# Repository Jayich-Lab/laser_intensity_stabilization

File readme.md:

# Laser Intensity Stabilization
<div align="center">

</div>

[Development Notebook](https://docs.google.com/document/d/1RtXi4E6TiI_Ld4MZSRgFrHrQVlKGbRzDl3qZmrDYwTk/edit#)

We are aiming to stabilize intensity of laser to a fluctuation range of plus-minus 1% using Acousto-Optic Modulator (AOM) for a long timescale (in the order of days). This stabilization will improve the precision of experiments that use laser beams.

## Table of Contents
- [Motivation](#Motivation)
  - [P 3/2 Life Measurement](#P-32-Life-Measurement)
  - [Problems](#Problems)
  - [Goal](#Goal)
- [List of Components](#List-of-Components)
- [Schematics](#Schematics)
  - [Experiment Setup Schematics](#Experiment-Setup-Schematics)
  - [Acousto-Optics Modulator (AOM)](#Acousto-Optics-Modulator-AOM)
  - [Red Pitaya](#Red-Pitaya)
  - [Voltage Variable Attenuator (VVA)](#Voltag-Variable-Attenuator-VVA)
- [Feedback Loop](#Feedback-Loop)
  - [PID Controller](#PID-Controller)
  - [Code](#Code)
  - [Continuous (CW) Feedback](#Continuous-CW-Feedback)
  - [Pulsed Feedback](#Pulsed-Feedback)
- [Iterations](#Iterations)
  - [PI Stabilization](#PI-Stabilization)
  - [I Stabilization](#I-Stabilization)
- [Future Plans](#Future-Plans)
- [Contributors](#Contributors)

# Motivation
## P 3/2 Life Measurement
<div align="center">

</div>
We want to measure the lifetime of the P 3/2 lifetime of the radium-226 ion. For this measurement, we need to stabilize a detuned 802 nm laser which will be used for probing the  D 5/2 to P 3/2 transitions. The need for laser intensity stabilization comes from the concept of Rabi flopping. When we raise an ion from its ground state to an excited state, it doesn’t simply remain excited; rather, it oscillates back and forth from the ground state to the excited state at a frequency known as the Rabi frequency. The Rabi frequency is directly proportional to the laser intensity. If the laser intensity is not stable, then the excitation oscillation will shift. We will end up with ions between the excited and ground state, which will increase the systematic errors in our measurements. 

## Problems
Laser intensity drifts with time, and the amplitude drift could result in un-precise energy level transition, which affects energy shift induced by ac-stark shift of detuned laser. This unstable laser intensity affects the precision of Ra-226 excitation.

## Goal
Our goal for this research is to find a laser stabilization method that works for any lasers with any desired intensity. Users are able to manually set the desired intensity. The proportional and integral constants in the PID controller will be able to change on its own corresponding to the input signals.

# List of Components

- Photo Diode: [PDA10A2](https://www.thorlabs.com/thorproduct.cfm?partnumber=PDA10A2)
- Acousto Optic Modulator: [ATM-802DA1](https://intraaction.com/wp-content/themes/Divi/pdf/ATMModSeries08991.pdf)
- Laser: [SYNCROLASE-100](https://en.yuyiparts.com/aerotech-syncrolase-100-helium-neon-laser.html)
- Voltage Controlled Oscillator: [ZX95-100-S+](https://www.minicircuits.com/WebStore/dashboard.html?model=ZX95-100-S%2B)
- Voltage Variable Attenuator: [ZX73-2500-S+](https://www.minicircuits.com/WebStore/dashboard.html?model=ZX73-2500-S%2B)
- RF Amplifier: [ZHL-1-2W+](https://www.minicircuits.com/WebStore/dashboard.html?model=ZHL-1-2W%2B)

# Schematics
## Experiment Setup Schematics
<div align="center">

</div>

First, the laser beam [1] is transmitted by the fiber and goes through the two fiber ports [2]. It then is received by the [Acousto-Optic Modulator (AOM)](#Acousto-Optics-Modulator-AOM) [3], which diffracts the light to different intensity. We use the first order beam in our project. Next, the beam coming out from the AOM goes through the PBS (Polarizing Beam Splitter) [4] and the NPBS (Non-Polarizing Beam Splitter) [5]. These two beam splitters split the light and control the amount of light that goes into the ion trap [6] and the photodiode [7]. We choose an NPBS that splits 90 percent of the light and lets 10 percent of the power go into the photodiode. The photodiode is the detector of laser intensity in our project. It converts the light signal into voltage, which can then be received and analyzed by the PID program in Red Pitaya. The photodiode generates a voltage signal in the range of ± 4 volts and outputs it to the Red Pitaya. A ¼ divider [8] is put between the photodiode and the Red Pitaya to compensate the limitation that Red Pitaya can only take a voltage from -1 to 1 volt. A PID program is built in [Red Pitaya](#Red-Pitaya) [9]. It collects signals from the photodiode and compares it to a setpoint voltage to create an error signal. The Red Pitaya will then return this DC gain error signal and send it to a [voltage variable attenuator (VVA)](#Voltage-Variable-Attenuator-VVA) [10]. VVA receives this DC gain signal as well as an RF reference signal sent from the VCO (voltage control oscillator) [11], and it will output an attenuated RF gain with attenuation determined by the input control voltage (see the attenuation graph in the VVA section). The RF gain is then amplified by an RF amplifier [12] and sent back into the AOM to alter the intensity that goes through it.

## Acousto-Optics Modulator (AOM)
<div align="center">

</div>

An AOM uses the acousto-optic effect, which is similar to the Bragg diffraction, to diffract and shift the frequency of the incident light. The acousto-optic effect describes the diffraction of light by acoustic waves. The basis of this effect is a general effect of photoelasticity consisting in the change of the medium permittivity under the action of a mechanical strain. With the acousto-optic effect, the amount of light diffracted by the sound wave depends on the intensity of the sound. Thus, we use the intensity of the sound to modulate the intensity of the light.

For our project, we choose the first order beam from the AOM. The difference between each order beam is that they have different dynamic ranges. The dynamic range is the ratio between the largest and smallest values of the intensity that can be outputted by the AOM. For the zeroth order beam, the intensity can be attenuated from 100 percent to 20 percent, which provides a dynamic range from 100 to 300; while for the first order beam, the intensity can be attenuated from 85 percent to 0 percent, which provides a dynamic range from 100 all the way to infinity. Thus, we choose the first order beam for our project to have a larger dynamic range.

The intensity of the first order beam is controlled by the control signal that goes into the AOM. When the control signal increases, the intensity increases correspondingly. We adjust the intensity of the laser using this property of the AOM.

## Red Pitaya
<div align="center">

</div>

Red Pitaya is an affordable, PC based, multi instrument. It acts as the brain of our project, which takes up the role of PID controller for the feedback loop (Discussed in Feedback Loop Section). Signal coming from the photodiode is received by the DAC portal of the Red Pitaya, and after the PID program an output signal will be sent out from the ADC portal to the voltage variable attenuator (VVA).

## Voltage Variable Attenuator (VVA)
<div align="center">

</div>

Attenuators are transmission line components used to reduce the input power in a system by a predetermined amount. It is operated throughout its entire dynamic range. Different from fixed attenuators, variable attenuators can be controlled to vary the attenuation level of the device with a number of different methods. A voltage variable attenuator, the VVA, has its attenuation controlled by the voltage. The typical attenuation of the VVA we use, ZX73-2500+ attenuator, is shown in the figure below.
<br>
<div align="center">

</div>

From the figure above, we can see that the attenuation of our ZX73-2500+ attenuator is non-linear, with the curve relatively linear and flat at control voltage range 0 to 0.5 volts and at high voltage. These linear regions imply that at these two control voltage ranges, the attenuation of the VVA does not change dramatically under large control voltage change. This property of the VVA helps to diminish the overcompensation of the PID program and prevent it from destroying the whole feedback loop. An overcompensation of the PID program means that the PID overcompensates for every positive error and creates an even larger error in the negative direction (and vice-versa). With a VVA in the circuit, the overcompensation from the PID feedback can be diminished and it will not cause serious failure in the stabilization. To achieve high precision, we require the input control signal at higher voltage. We choose 4-12 volts as our range of control voltage in our project.

# Feedback Loop
## PID Controller
<div align="center">

</div>

Red Pitaya is remotely controlled using a client on a computer via an internal network. After receiving the signal, the pitaya runs a python script (discussed in [Code](#Code)) section, compares the input voltage to the setpoint voltage, and applies a control signal, C, which depends on the proportional, integral and differential terms of the error signal. The relationship can be seen in the equation above. We neglected the differential term for our setup as we weren’t concerned with stabilizing at high frequency (laser fluctuations tended to be low frequency). The control signal from the pitaya goes through an operational amplifier which increases the control range from ± 1 volt to 4 and 12 volts. The [Voltage Variable Attenuator (VVA)](#Voltage-Variable-Attenuator-VVA) section explains why we want to be in the 4 -12 voltage range. The control signal was also sent to an oscilloscope at the same time. The majority of the data was taken on an oscilloscope. The data from the oscilloscope was read by a server on the computer and sent to the red pitaya. The computer (server and client) are constantly communicating with the red pitaya during  the feedback loop. 

## Code
The programming was mainly done on the red pitaya using python and the PyRPL module, which has python defined classes for controlling the pitaya outputs and inputs. The PyRPL code was written onto a server, and a client was then made using that server. 
There was also a simpler script made for an independent laser intensity stabilization setup using an Arduino due. The code is above under “PI_Stabilization.ino”. The Arduino presents versatility as it uses C++, a widely accessible programming language. On the other hand, the red pitaya can either be programmed using the limited PYRPL module or the native language of the pitaya, Verilog, which is less accessible. 
Either the Arduino or the pitaya is sufficient for stabilization. Still, when it comes to pulsed feedback (discussed shortly), the Arduino is a better choice as C++ is easier to work with than Verilog. 

## Continuous (CW) Feedback
<div align="center">

</div>

We need to identify a clear distinction between continuous and pulsed feedback. In this experiment, we are applying continuous waveform (CW) feedback. We are continuously reading data and stabilizing it over time. The picture above illustrates a summary of our CW feedback in a rectangle on the right. Generally, in ion trap experiments, laser beams are sent to the ion trap in pulse sequences (on the order of microseconds). We can create a stabilized pulsing laser by placing a second AOM after the laser is stabilized. The second AOM will receive a signal that turns it “on” or “off,” This way, we have a pseudo pulsed feedback setup. 

## Pulsed Feedback
<div align="center">

</div>
We created pseudo pulsed feedback, but what does pulsed feedback look like? Unlike CW feedback, in pulsed feedback, we only take data on short intervals (µs). The above graph models a pulse sequence where the laser is on for µs and off for ms. During the period the laser is on, a microcontroller collects data and generates an error signal E1. When the laser is off, the microcontroller outputs a constant dc offset. After the laser is turned on again, a fixed dc voltage (red line) is outputted based on the error signal E1. This process continues for all pulses.
<br>
*Note only CW feedback was used in this project 

# Iterations
## PI Stabilization
<div align="center">

</div>
<br>

Laser intensity was stabilized to ± 0.2%, which surpasses our goal of ± 1%. The blue plot is the signal received by the photodiode, the orange curve is the control signal output by the red pitaya, and the green line is the stabilized signal.  We took the data in 8 hours and found no drifts in the stabilization, which indicates that our setup is robust since it maintains the same intensity while environmental parameters such as temperature change. Using only the P and I terms, we were able to minimize the initial noise by a factor of 200. 
<br><br>

<div align="center">

</div>
<br>

Looking more closely at the stabilized signal, we can see no long-term drift; the signal only oscillates at high frequency. This high-frequency noise can be accounted for by the internal noise of the photodiode. The ± 0.2% fluctuation in our data was partly correlated to the photodiode uncertainty; the rest of the noise comes from the control signal output by the pitaya. The above data set was preliminary data and demonstrated the sufficiency of our stabilization for the P 3/2 life measurement. 

## I Stabilization
<div align="center">

</div>

Using 802 nm laser light (20% intensity fluctuation without stablilization), we stablilized the laser to average within ± 0.1% of our setpoint intensity. Extreme peaks during stablization still stayed within ± 0.3% of setpoint.  Long term drift of intensity from 802 nm is no longer a problem with this intensity stabilizer. The graph above was taken  on the laser that was used for the P 3/2 life time measurement. 

Observations:
1. It was found that **omitting** the proportional term for PID control was more stable than including proportional control.
2. The lower the control voltage (shown in the bottom graph as it slopes downward), the less stablity we get due to the VVA response curve at different voltages.

# Future Plans
<div align="center">

</div>
<br>

There are some issues with our current pseudo pulsed feedback setup. 1) We can’t stabilize the laser intensity right before the beam reaches the ion trap; it has to go through different optics before reaching the trap, which means it will incur some extra noise that we can’t currently stabilize. 2) The second AOM (the one receiving pulsed signal) changes how fast it can turn on and off based on the environmental temperature. 3) Our current setup, as you can see from the picture above, uses too many separate power supplies, which makes it difficult to set up and apply to any measurement. 
Potential solution: utilize an [Arduino DUE](https://store.arduino.cc/usa/due) to make independent pulsed feedback. This would eliminate the second AOM and allow us to stabilize the laser light right before it reaches the ion trap.We would also be able to make an integrated power supply, making our stabilization more compact and robust. 

# Contributors
This project is made for CS 15C class by Chaoshen Zhang, Sam Gebretsadkan, Vivian Liao and Rei Landsberger.

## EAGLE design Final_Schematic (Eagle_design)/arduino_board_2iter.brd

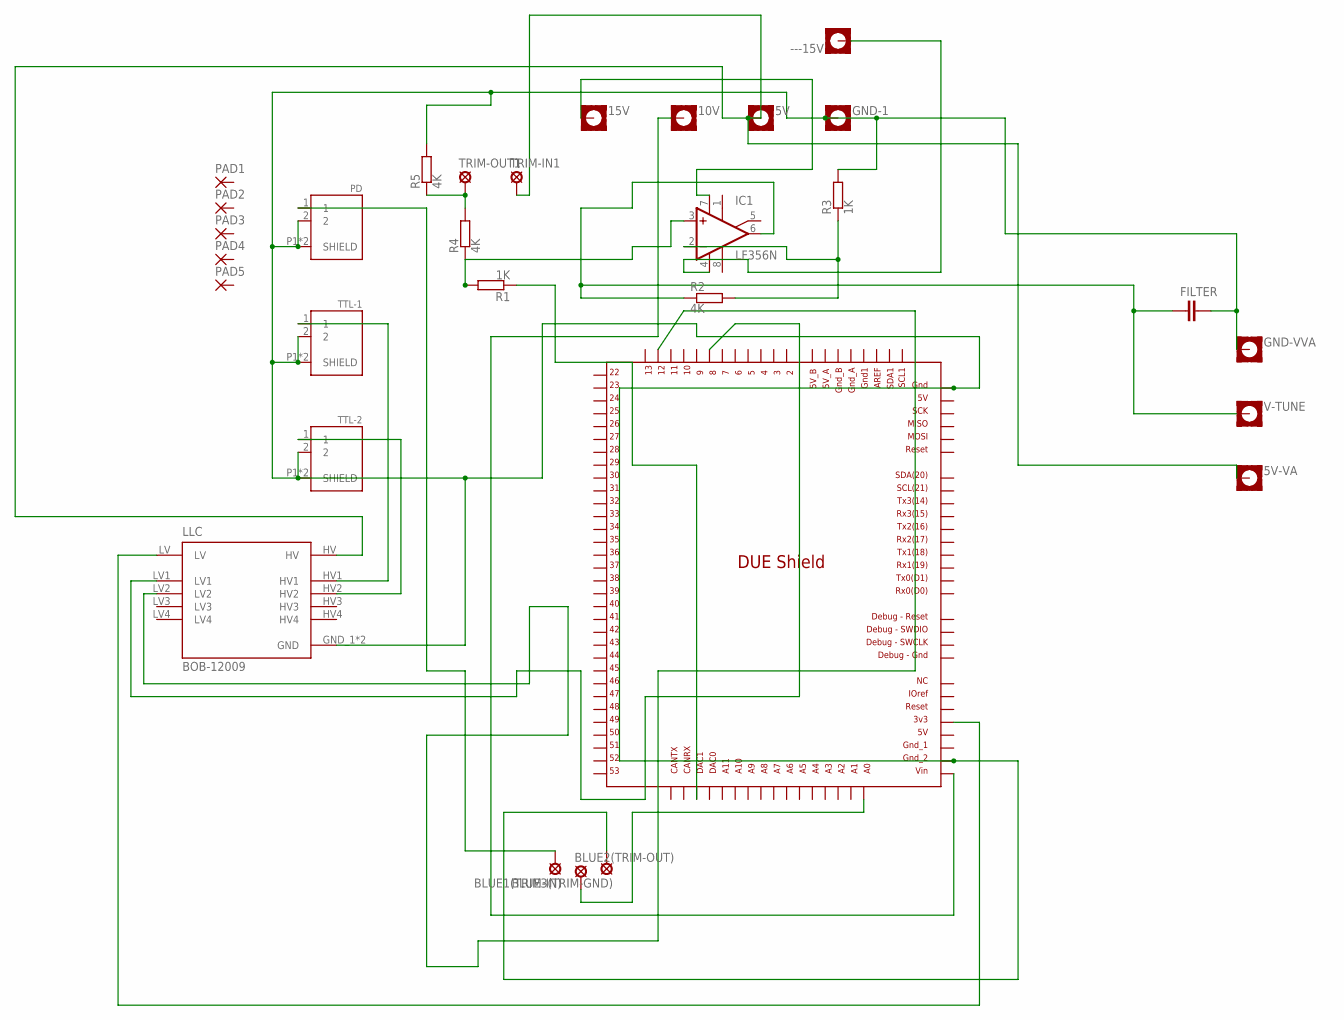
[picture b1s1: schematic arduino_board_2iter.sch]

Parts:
5V, 5V-VA, 10V, 15V: MOUNT-PAD-SQUARE2.8; 2,8-PAD-SQUARE
---15V: MOUNT-PAD-SQUARE2.8; 2,8-PAD-SQUARE
BLUE1(TRIM-IN), BLUE2(TRIM-OUT), BLUE3(TRIM-GND): LSP10
FILTER: C-EUC1812K; C1812K
GND-1: MOUNT-PAD-SQUARE2.8; 2,8-PAD-SQUARE
GND-VVA: MOUNT-PAD-SQUARE2.8; 2,8-PAD-SQUARE
IC1: LF356N; DIL08
LLC: BOB-12009; CONV_BOB-12009
PAD1, PAD2, PAD3, PAD4, PAD5: 1,6/0,9
PD: 1-1337543-0; CONN_1-1337543-0
R1, R3: 1K; SMS-0
R2, R4, R5: 4K; SMS-0
TRIM-IN1: LSP10
TRIM-OUT1: LSP10
TTL-1, TTL-2: 1-1337543-0; CONN_1-1337543-0
U$1: DUE(NORMAL)
V-TUNE: MOUNT-PAD-SQUARE2.8; 2,8-PAD-SQUARE

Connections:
GND: BLUE3(TRIM-GND).MP, FILTER.2, GND-1.B2,8, GND-VVA.B2,8, LLC.GND_1 (GND), LLC.GND_2 (GND), PD.2, PD.P1 (SHIELD), PD.P2 (SHIELD), R3.1, R5.1, TTL-1.2, TTL-1.P1 (SHIELD), TTL-1.P2 (SHIELD), TTL-2.2, TTL-2.P1 (SHIELD), TTL-2.P2 (SHIELD), U$1.5V_ICSP, U$1.GND_2
unnamed: IC1.3 (+IN), R1.1, R4.2
unnamed: FILTER.1, IC1.6 (OUT), R2.2, V-TUNE.B2,8
unnamed: IC1.2 (-IN), R2.1, R3.2
unnamed: 10V.B2,8, U$1.VIN
unnamed: R1.2, U$1.DAC1
unnamed: 15V.B2,8, IC1.7 (V+)
unnamed: LLC.LV, U$1.3V3
unnamed: LLC.HV1, TTL-1.1
unnamed: LLC.HV2, TTL-2.1
unnamed: BLUE1(TRIM-IN).MP, PD.1
unnamed: 5V.B2,8, 5V-VA.B2,8, LLC.HV, TRIM-IN1.MP
unnamed: LLC.LV2, U$1.12
unnamed: BLUE2(TRIM-OUT).MP, U$1.A0
unnamed: R4.1, R5.2, TRIM-OUT1.MP
unnamed: ---15V.B2,8, IC1.4 (V-)
unnamed: LLC.LV1, U$1.8

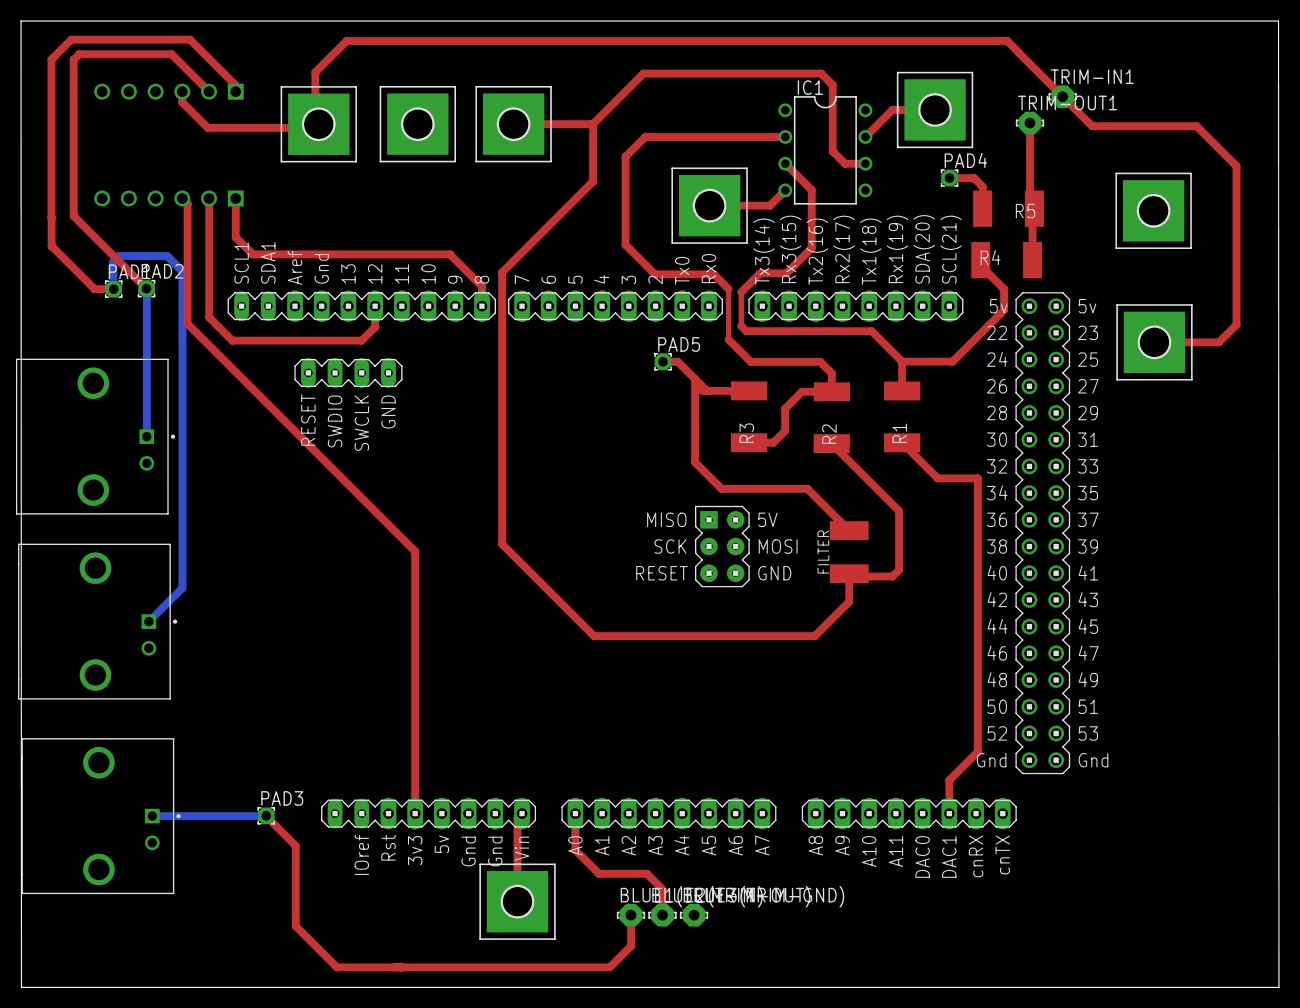
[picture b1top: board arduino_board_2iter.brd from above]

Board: 2 copper layers, 119.6 x 91.9 mm, 30 parts (1 on the bottom side), 17 nets.

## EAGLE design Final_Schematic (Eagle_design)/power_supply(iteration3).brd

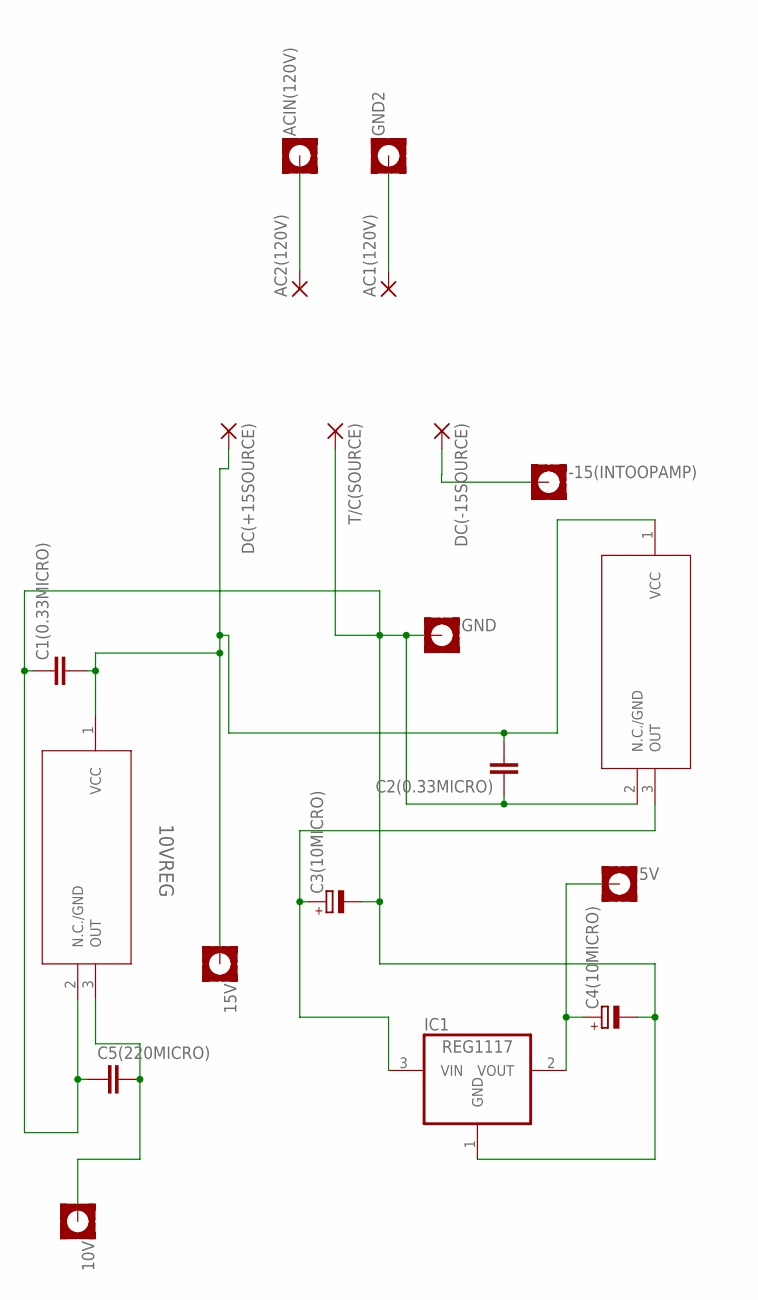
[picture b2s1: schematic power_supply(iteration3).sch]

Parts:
5V, 10V, 15V: MOUNT-PAD-SQUARE2.8; 2,8-PAD-SQUARE
10VREG, 10VREG1: BAJ0BC0T; TO220FP-3_ROM
-15(INTOOPAMP): MOUNT-PAD-SQUARE2.8; 2,8-PAD-SQUARE
AC1(120V), AC2(120V): 3,81/1,4
ACIN(120V): MOUNT-PAD-SQUARE2.8; 2,8-PAD-SQUARE
C1(0.33MICRO), C2(0.33MICRO): C-EU025-025X050; C025-025X050
C3(10MICRO), C4(10MICRO): CPOL-EUE2.5-6; E2,5-6
C5(220MICRO): C-EUC1812K; C1812K
DC(+15SOURCE): 3,81/1,4
DC(-15SOURCE): 3,81/1,4
GND, GND2: MOUNT-PAD-SQUARE2.8; 2,8-PAD-SQUARE
IC1: REG1117; SOT223_HEATSINK
T/C(SOURCE): 3,81/1,4

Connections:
unnamed: 10VREG.1 (VCC), 10VREG1.1 (VCC), 15V.B2,8, C1(0.33MICRO).2, C2(0.33MICRO).2, DC(+15SOURCE).1
unnamed: 10V.B2,8, 10VREG.3 (OUT), C5(220MICRO).2
unnamed: AC2(120V).1, ACIN(120V).B2,8
unnamed: 10VREG1.3 (OUT), C3(10MICRO).+, IC1.3 (VIN)
unnamed: AC1(120V).1, GND2.B2,8
unnamed: -15(INTOOPAMP).B2,8, DC(-15SOURCE).1
unnamed: 10VREG.2 (N.C./GND), 10VREG1.2 (N.C./GND), C1(0.33MICRO).1, C2(0.33MICRO).1, C3(10MICRO).-, C4(10MICRO).-, C5(220MICRO).1, GND.B2,8, IC1.1 (GND), T/C(SOURCE).1
unnamed: 5V.B2,8, C4(10MICRO).+, IC1.2 (VOUT)

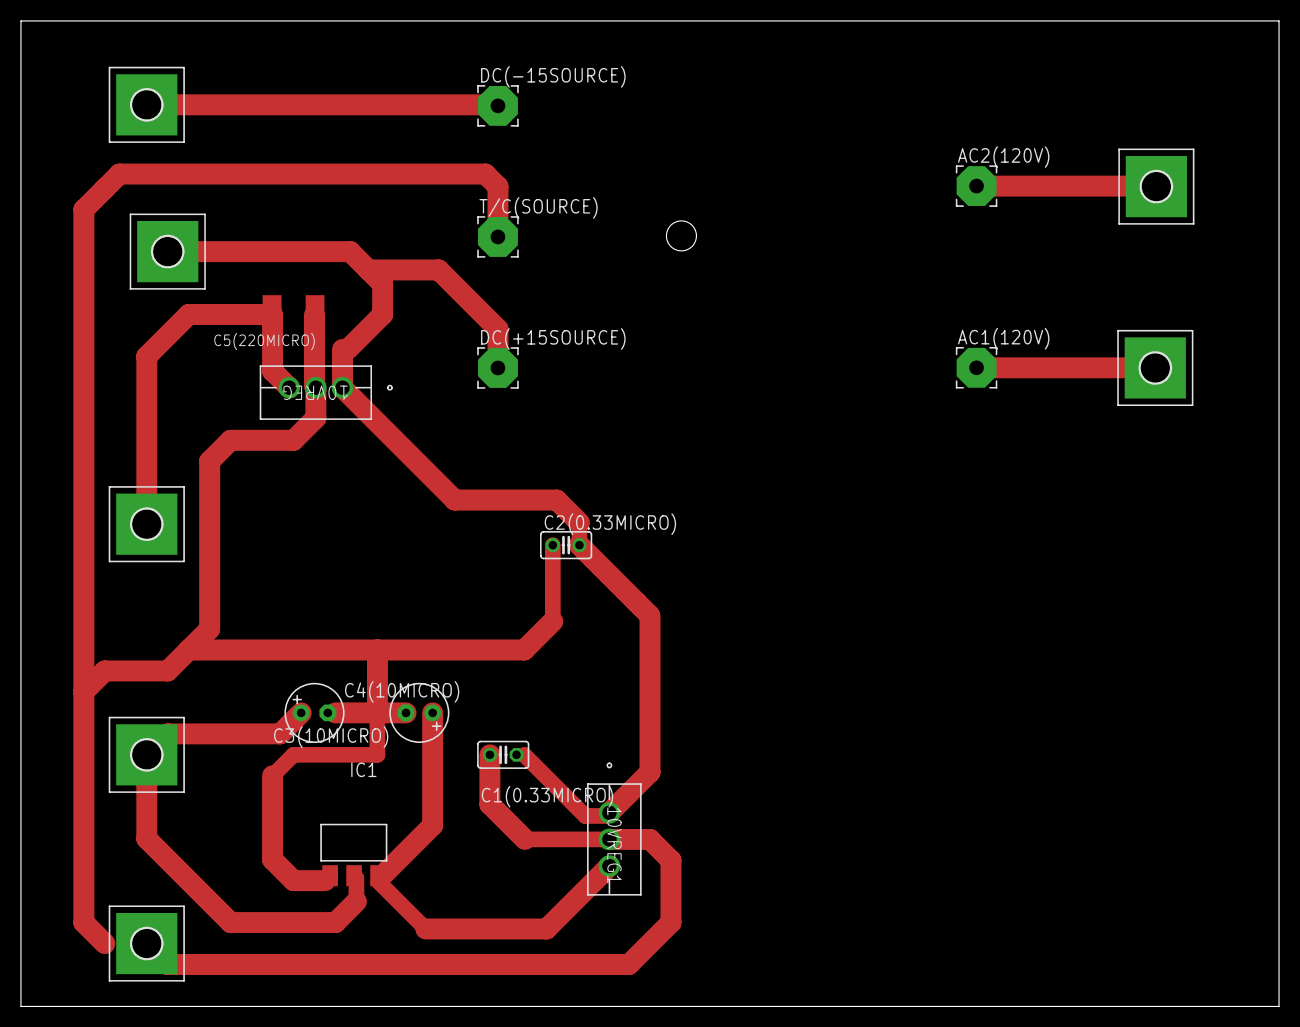
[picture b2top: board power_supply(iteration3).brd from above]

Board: 2 copper layers, 120.0 x 94.0 mm, 20 parts (0 on the bottom side), 8 nets.

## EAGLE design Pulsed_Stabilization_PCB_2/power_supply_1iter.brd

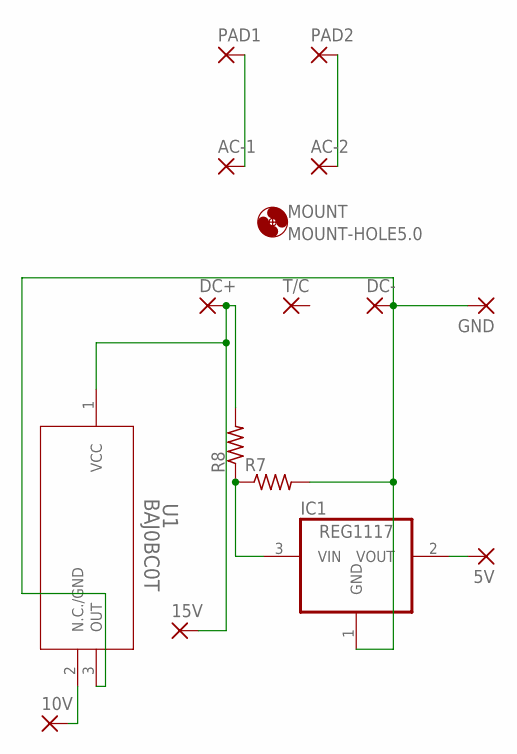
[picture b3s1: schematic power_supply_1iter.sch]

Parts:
5V, 10V, 15V: 3,17/1,1
AC-1, AC-2: 3,81/1,1
DC+: 3,81/1,1
DC-: 3,81/1,1
GND: 3,17/1,1
IC1: REG1117; SOT223_HEATSINK
MOUNT: MOUNT-HOLE5.0; 5,0
PAD1, PAD2: WIREPAD4,16O1,6; 4,16O1,6
R7, R8: R-US_0309/12; 0309/12
T/C: 3,81/1,1
U1: BAJ0BC0T; TO220FP-3_ROM

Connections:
unnamed: AC-1.1, PAD1.1
unnamed: AC-2.1, PAD2.1
unnamed: 15V.1, DC+.1, R8.2, U1.1 (VCC)
unnamed: DC-.1, GND.1, IC1.1 (GND), R7.2, U1.3 (OUT)
unnamed: IC1.3 (VIN), R7.1, R8.1
unnamed: 10V.1, U1.2 (N.C./GND)
unnamed: 5V.1, IC1.2 (VOUT)

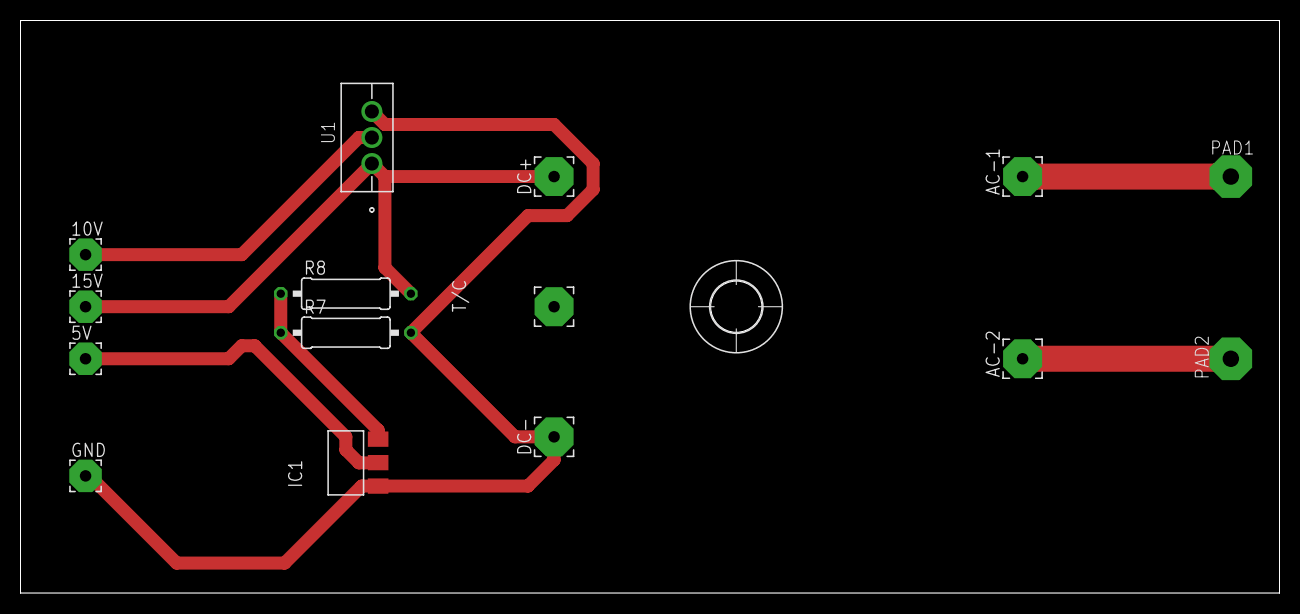
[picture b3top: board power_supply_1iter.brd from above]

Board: 2 copper layers, 122.9 x 55.9 mm, 16 parts (0 on the bottom side), 7 nets.

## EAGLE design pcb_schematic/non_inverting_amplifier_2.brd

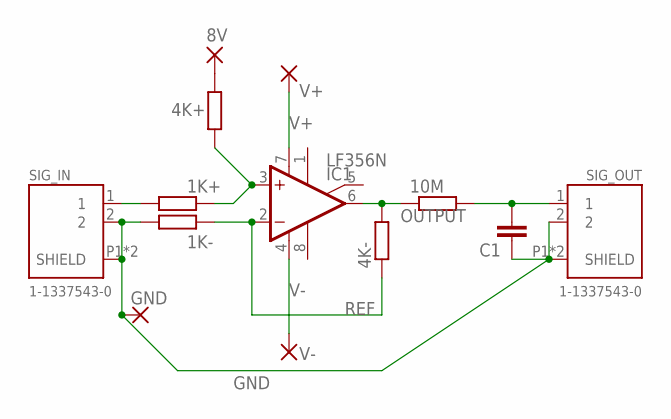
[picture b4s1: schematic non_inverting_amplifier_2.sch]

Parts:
1K+, 1K-, 4K+, 4K-, 10M: R-EU_0207/12; 0207/12
8V: 2,54/1,1
C1: C2,5-3; C2.5-3
GND: 2,54/1,1
IC1: LF356N; DIL08
SIG_IN: 1-1337543-0; CONN_1-1337543-0
SIG_OUT: 1-1337543-0; CONN_1-1337543-0
V+: 2,54/1,1
V-: 2,54/1,1

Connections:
GND: 1K-.1, C1.1, GND.1, SIG_IN.2, SIG_IN.P1 (SHIELD), SIG_IN.P2 (SHIELD), SIG_OUT.2, SIG_OUT.P1 (SHIELD), SIG_OUT.P2 (SHIELD)
unnamed: 1K+.1, SIG_IN.1
unnamed: 1K+.2, 4K+.1, IC1.3 (+IN)
unnamed: 4K+.2, 8V.1
unnamed: 10M.2, C1.2, SIG_OUT.1
OUTPUT: 4K-.2, 10M.1, IC1.6 (OUT)
REF: 1K-.2, 4K-.1, IC1.2 (-IN)
V+: IC1.7 (V+), V+.1
V-: IC1.4 (V-), V-.1

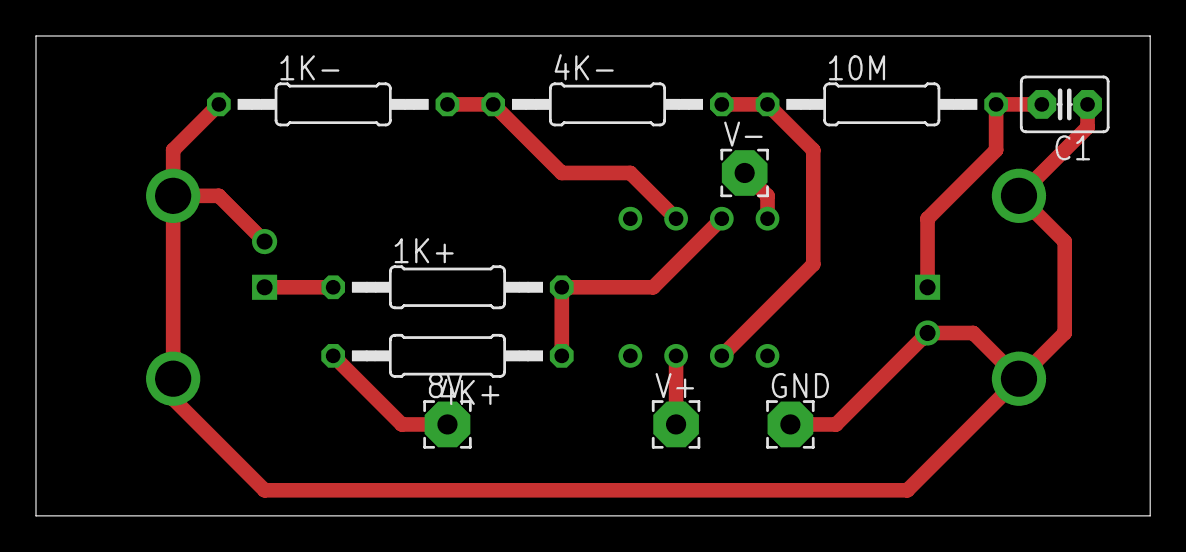
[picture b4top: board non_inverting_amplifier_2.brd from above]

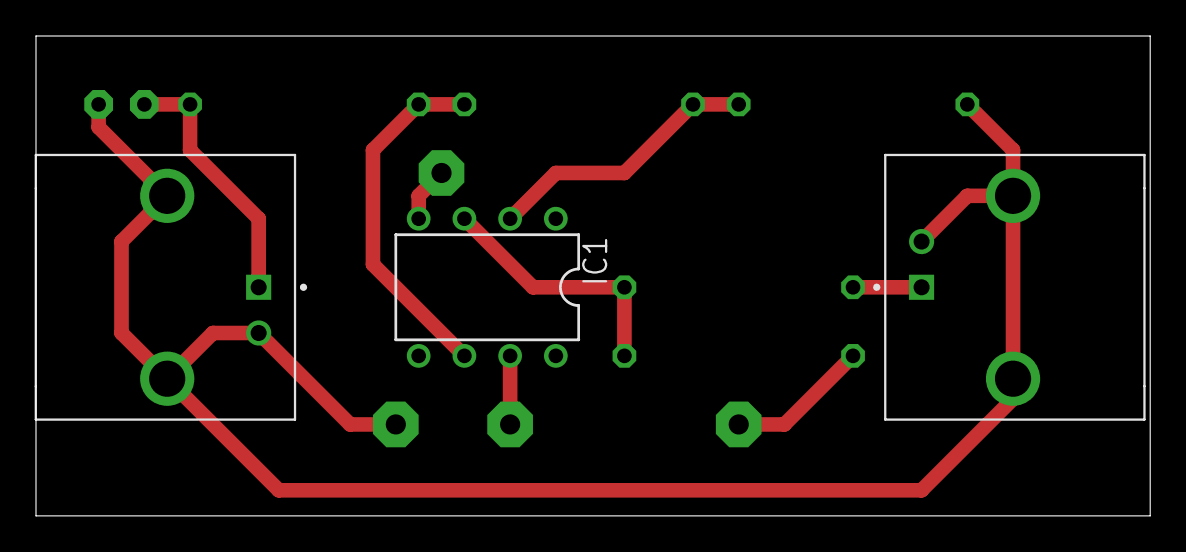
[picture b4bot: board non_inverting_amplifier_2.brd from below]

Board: 2 copper layers, 61.9 x 26.7 mm, 13 parts (3 on the bottom side), 9 nets.

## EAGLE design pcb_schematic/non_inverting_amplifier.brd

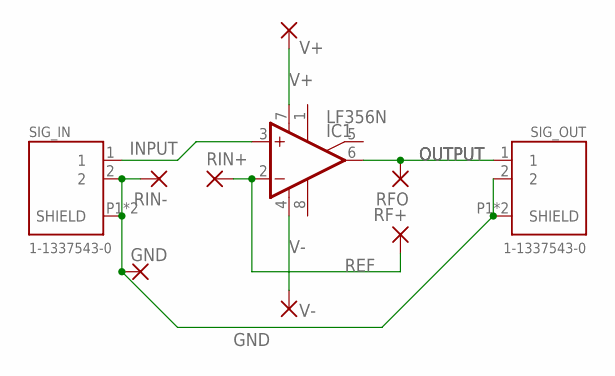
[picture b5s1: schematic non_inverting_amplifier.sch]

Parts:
GND: 2,54/1,1
IC1: LF356N; DIL08
RF+: 2,54/1,1
RFO: 2,54/1,1
RIN+: 2,54/1,1
RIN-: 2,54/1,1
SIG_IN: 1-1337543-0; CONN_1-1337543-0
SIG_OUT: 1-1337543-0; CONN_1-1337543-0
V+: 2,54/1,1
V-: 2,54/1,1

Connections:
GND: GND.1, RIN-.1, SIG_IN.2, SIG_IN.P1 (SHIELD), SIG_IN.P2 (SHIELD), SIG_OUT.2, SIG_OUT.P1 (SHIELD), SIG_OUT.P2 (SHIELD)
INPUT: IC1.3 (+IN), SIG_IN.1
OUTPUT: IC1.6 (OUT), RFO.1, SIG_OUT.1
REF: IC1.2 (-IN), RF+.1, RIN+.1
V+: IC1.7 (V+), V+.1
V-: IC1.4 (V-), V-.1

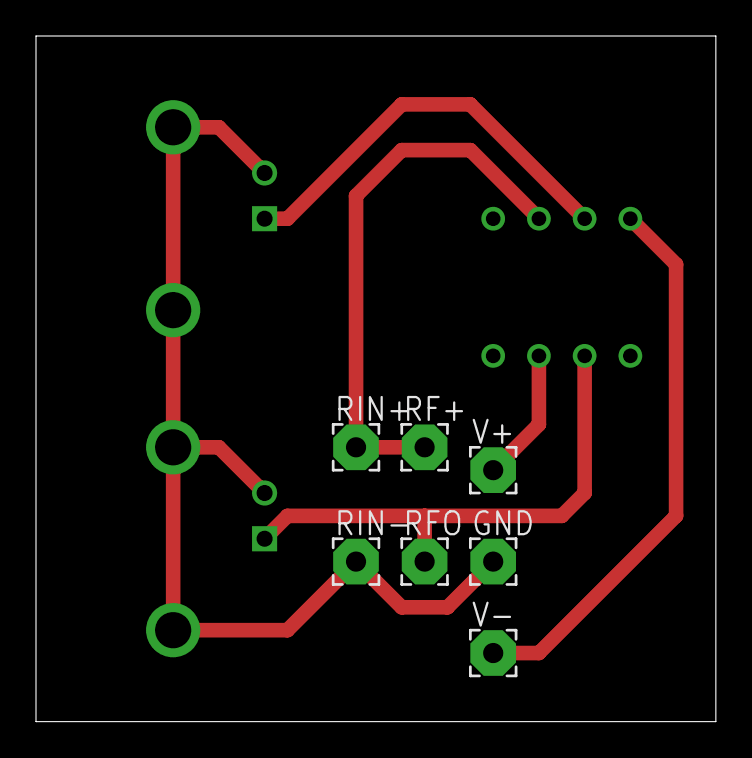
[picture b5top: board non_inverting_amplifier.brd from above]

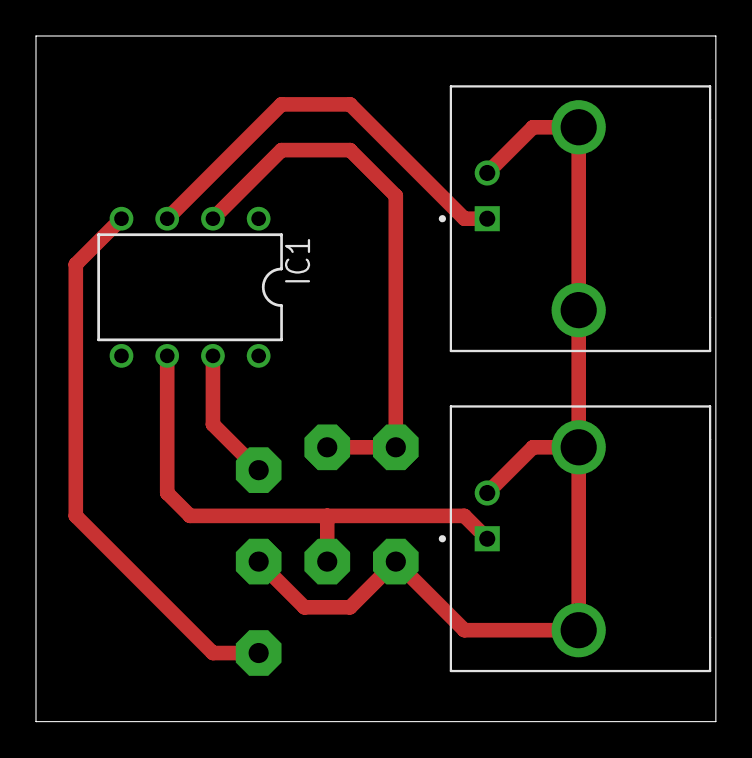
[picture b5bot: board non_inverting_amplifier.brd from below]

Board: 2 copper layers, 37.8 x 38.1 mm, 10 parts (3 on the bottom side), 6 nets.

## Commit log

2021-05-23 amp iteration 2
2021-06-16 Update on pulsed stabilization
2022-07-27 Updated PCB Schematics
2022-07-29 Updated PCBs
2022-08-04 Updated Arduino PCB for larger size
2022-08-04 PCB Updates as of 8/4/22
2022-08-05 Updated PCB
2022-08-09 PCB Updates as of 8/9/22

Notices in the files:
parts and their libraries:
COPYRIGHT: Copyright (C) 2018 Accelerated Designs. All rights reserved
